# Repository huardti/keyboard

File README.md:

# zigzag keyboard

kle layout : http://www.keyboard-layout-editor.com/#/gists/5584793507362f9928e871f4f528520b

to see connections : https://kbfirmware.com/

# QMK help : 
https://github.com/qmk/keyboard_awesome

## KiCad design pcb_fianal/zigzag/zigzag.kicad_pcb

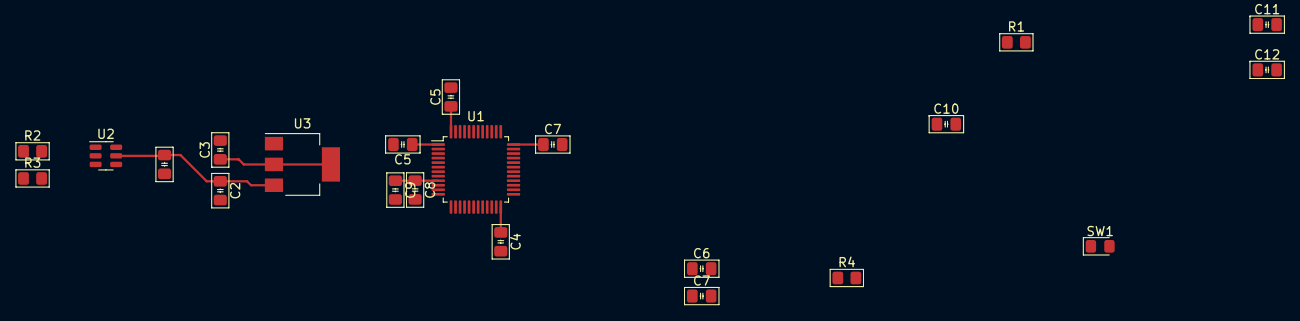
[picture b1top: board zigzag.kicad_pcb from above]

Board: 2 copper layers, 22 parts (0 on the bottom side), 5 nets.

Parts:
C1, C4, C5, C5#2, C6, C7, C7#2: 100nF; C_0805_2012Metric_Pad1.18x1.45mm_HandSolder
C2, C3: 10uF; C_0805_2012Metric_Pad1.18x1.45mm_HandSolder
C8: 1uF; C_0805_2012Metric_Pad1.18x1.45mm_HandSolder
C9: 10nF; C_0805_2012Metric_Pad1.18x1.45mm_HandSolder
C10: C_4.7uF; C_0805_2012Metric_Pad1.18x1.45mm_HandSolder
C11, C12: 30pF; C_0805_2012Metric_Pad1.18x1.45mm_HandSolder
R1: 470; R_0805_2012Metric_Pad1.20x1.40mm_HandSolder
R2, R3: 5.1k; R_0805_2012Metric_Pad1.20x1.40mm_HandSolder
R4: 10k; R_0805_2012Metric_Pad1.20x1.40mm_HandSolder
SW1: SW_Push; D_0805_2012Metric_Pad1.15x1.40mm_HandSolder
U1: STM32F303CCTx; LQFP-48_7x7mm_P0.5mm
U2: USBLC6-2SC6; SOT-23-6
U3: NCP1117-3.3_SOT223; SOT-223-3_TabPin2

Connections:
+3.3V: C3.1, C4.1, C5.1, C5#2.1, C6.1, C7.1, C7#2.1, SW1.1, U1.1 (VBAT), U1.24 (VDD), U1.36 (VDD), U1.48 (VDD), U3.2 (VO)
BOOT0: R4.2, SW1.2
GND: C1.2, C2.2, C3.2, C4.2, C5.2, C5#2.2, C6.2, C7.2, C7#2.2, C8.2, C9.2, C10.2, C11.2, C12.2, R2.1, R3.1, R4.1, U1.8 (VSSA), U1.23 (VSS), U1.35 (VSS), U1.47 (VSS), U2.2 (GND), U3.1 (GND)
unnamed: C8.1, C9.1, U1.9 (VDDA)
VBUS: C1.1, C2.1, U2.5 (VBUS), U3.3 (VI)

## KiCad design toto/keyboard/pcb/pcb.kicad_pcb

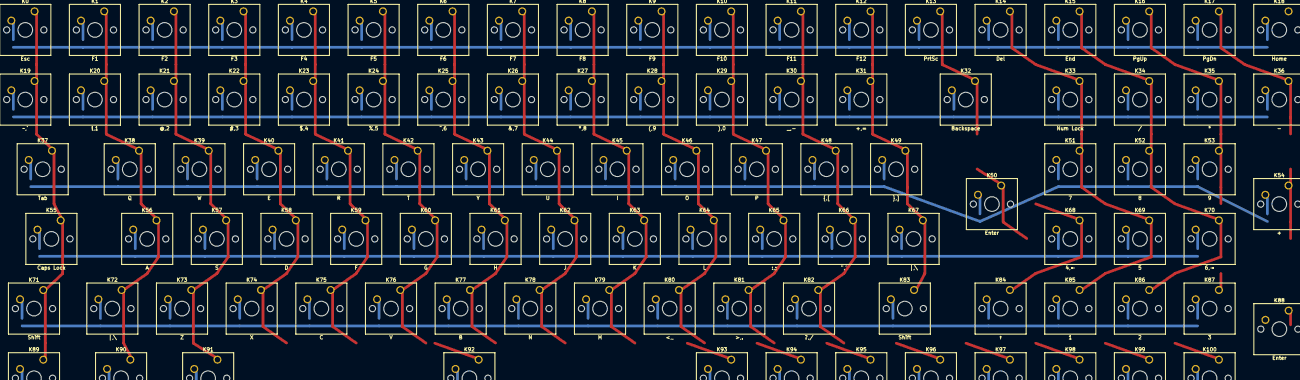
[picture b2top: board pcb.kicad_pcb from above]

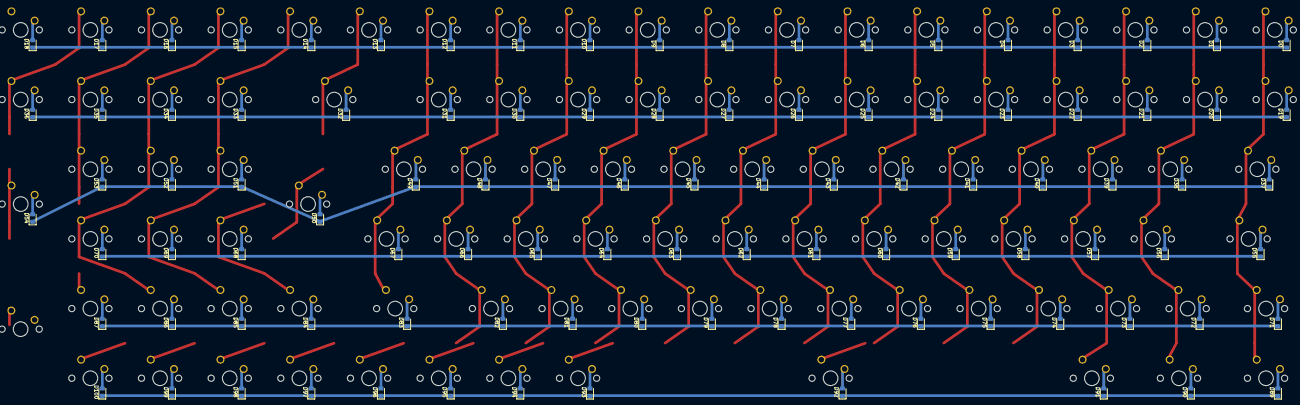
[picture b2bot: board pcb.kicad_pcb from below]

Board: 2 copper layers, 205 parts (100 on the bottom side), 124 nets.

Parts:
D0, D1, D2, D3, D4, D5, D6, D7, D8, D9, D10, D11, D12, D13, D14, D15, D16, D17, D18, D19, D20, D21, D22, D23, D24, D25, D26, D27, D28, D29, D30, D31, D32, D33, D34, D35, D36, D37, D38, D39, D40, D41, D42, D43, D44, D45, D46, D47, D48, D49, D50, D51, D52, D53, D54, D55, D56, D57, D58, D59, D60, D61, D62, D63, D64, D65, D66, D67, D68, D69, D70, D71, D72, D73, D74, D75, D76, D77, D78, D79, D80, D81, D82, D83, D84, D85, D86, D87, D89, D90, D91, D92, D93, D94, D95, D96, D97, D98, D99, D100: D; D_0805_2012Metric_Pad1.15x1.40mm_HandSolder
H1, H2, H3, H4: MountingHole; MountingHole_3.2mm_M3_DIN965
K0: Esc; SW_Cherry_MX_1.00u_PCB
K1: F1; SW_Cherry_MX_1.00u_PCB
K2: F2; SW_Cherry_MX_1.00u_PCB
K3: F3; SW_Cherry_MX_1.00u_PCB
K4: F4; SW_Cherry_MX_1.00u_PCB
K5: F5; SW_Cherry_MX_1.00u_PCB
K6: F6; SW_Cherry_MX_1.00u_PCB
K7: F7; SW_Cherry_MX_1.00u_PCB
K8: F8; SW_Cherry_MX_1.00u_PCB
K9: F9; SW_Cherry_MX_1.00u_PCB
K10: F10; SW_Cherry_MX_1.00u_PCB
K11: F11; SW_Cherry_MX_1.00u_PCB
K12: F12; SW_Cherry_MX_1.00u_PCB
K13: PrtSc; SW_Cherry_MX_1.00u_PCB
K14: Del; SW_Cherry_MX_1.00u_PCB
K15: End; SW_Cherry_MX_1.00u_PCB
K16: PgUp; SW_Cherry_MX_1.00u_PCB
K17: PgDn; SW_Cherry_MX_1.00u_PCB
K18: Home; SW_Cherry_MX_1.00u_PCB
K19: ~,`; SW_Cherry_MX_1.00u_PCB
K20: !,1; SW_Cherry_MX_1.00u_PCB
K21: @,2; SW_Cherry_MX_1.00u_PCB
K22: #,3; SW_Cherry_MX_1.00u_PCB
K23: $,4; SW_Cherry_MX_1.00u_PCB
K24: %,5; SW_Cherry_MX_1.00u_PCB
K25: ^,6; SW_Cherry_MX_1.00u_PCB
K26: &,7; SW_Cherry_MX_1.00u_PCB
K27: *,8; SW_Cherry_MX_1.00u_PCB
K28: (,9; SW_Cherry_MX_1.00u_PCB
K29: ),0; SW_Cherry_MX_1.00u_PCB
K30: _,-; SW_Cherry_MX_1.00u_PCB
K31: +,=; SW_Cherry_MX_1.00u_PCB
K32: Backspace; SW_Cherry_MX_2.00u_PCB
K33: Num Lock; SW_Cherry_MX_1.00u_PCB
K34: /; SW_Cherry_MX_1.00u_PCB
K35: *; SW_Cherry_MX_1.00u_PCB
K36: -; SW_Cherry_MX_1.00u_PCB
K37: Tab; SW_Cherry_MX_1.50u_PCB
K38: Q; SW_Cherry_MX_1.00u_PCB
K39: W; SW_Cherry_MX_1.00u_PCB
K40: E; SW_Cherry_MX_1.00u_PCB
K41: R; SW_Cherry_MX_1.00u_PCB
K42: T; SW_Cherry_MX_1.00u_PCB
K43: Y; SW_Cherry_MX_1.00u_PCB
K44: U; SW_Cherry_MX_1.00u_PCB
K45: I; SW_Cherry_MX_1.00u_PCB
K46: O; SW_Cherry_MX_1.00u_PCB
K47: P; SW_Cherry_MX_1.00u_PCB
K48: {,[; SW_Cherry_MX_1.00u_PCB
K49: },]; SW_Cherry_MX_1.00u_PCB
K50: Enter; SW_Cherry_MX_1.25u_PCB
K51: 7; SW_Cherry_MX_1.00u_PCB
K52: 8; SW_Cherry_MX_1.00u_PCB
K53: 9; SW_Cherry_MX_1.00u_PCB
K54: +; SW_Cherry_MX_1.00u_PCB
K55: Caps Lock; SW_Cherry_MX_1.75u_PCB
K56: A; SW_Cherry_MX_1.00u_PCB
K57: S; SW_Cherry_MX_1.00u_PCB
K58: D; SW_Cherry_MX_1.00u_PCB
K59: F; SW_Cherry_MX_1.00u_PCB
K60: G; SW_Cherry_MX_1.00u_PCB
K61: H; SW_Cherry_MX_1.00u_PCB
K62: J; SW_Cherry_MX_1.00u_PCB
K63: K; SW_Cherry_MX_1.00u_PCB
K64: L; SW_Cherry_MX_1.00u_PCB
K65: :,;; SW_Cherry_MX_1.00u_PCB
K66: ",'; SW_Cherry_MX_1.00u_PCB
K67, K72: |,\; SW_Cherry_MX_1.00u_PCB
K68: 4,←; SW_Cherry_MX_1.00u_PCB
K69: 5; SW_Cherry_MX_1.00u_PCB
K70: 6,→; SW_Cherry_MX_1.00u_PCB
K71: Shift; SW_Cherry_MX_1.25u_PCB
K73: Z; SW_Cherry_MX_1.00u_PCB
K74: X; SW_Cherry_MX_1.00u_PCB
K75: C; SW_Cherry_MX_1.00u_PCB
K76: V; SW_Cherry_MX_1.00u_PCB
K77: B; SW_Cherry_MX_1.00u_PCB
K78: N; SW_Cherry_MX_1.00u_PCB
K79: M; SW_Cherry_MX_1.00u_PCB
K80: <,,; SW_Cherry_MX_1.00u_PCB
K81: >,.; SW_Cherry_MX_1.00u_PCB
K82: ?,/; SW_Cherry_MX_1.00u_PCB
K83: Shift; SW_Cherry_MX_1.75u_PCB
K84: ↑; SW_Cherry_MX_1.00u_PCB
K85: 1; SW_Cherry_MX_1.00u_PCB
K86: 2; SW_Cherry_MX_1.00u_PCB
K87: 3; SW_Cherry_MX_1.00u_PCB
K88: Enter; SW_Cherry_MX_1.00u_PCB
K89: Ctrl; SW_Cherry_MX_1.25u_PCB
K90: Win; SW_Cherry_MX_1.25u_PCB
K91: Alt; SW_Cherry_MX_1.25u_PCB
K92: Blank; SW_Cherry_MX_6.25u_PCB
K93: Alt; SW_Cherry_MX_1.00u_PCB
K94: Fn; SW_Cherry_MX_1.00u_PCB
K95: Ctrl; SW_Cherry_MX_1.00u_PCB
K96: ←; SW_Cherry_MX_1.00u_PCB
K97: ↓; SW_Cherry_MX_1.00u_PCB
K98: →; SW_Cherry_MX_1.00u_PCB
K99: 0; SW_Cherry_MX_1.00u_PCB
K100: .; SW_Cherry_MX_1.00u_PCB

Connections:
/Col_0: K0.1, K19.1, K37.1, K55.1, K71.1, K89.1
/Col_1: K1.1, K20.1, K38.1, K56.1, K72.1, K90.1
/Col_2: K2.1, K21.1, K39.1, K57.1, K73.1, K91.1
/Col_3: K3.1, K22.1, K40.1, K58.1, K74.1, K92.1
/Col_4: K4.1, K23.1, K41.1, K59.1, K75.1, K93.1
/Col_5: K5.1, K24.1, K42.1, K60.1, K76.1, K94.1
/Col_6: K6.1, K25.1, K43.1, K61.1, K77.1, K95.1
/Col_7: K7.1, K26.1, K44.1, K62.1, K78.1, K96.1
/Col_8: K8.1, K27.1, K45.1, K63.1, K79.1, K97.1
/Col_9: K9.1, K28.1, K46.1, K64.1, K80.1, K98.1
/Col_10: K10.1, K29.1, K47.1, K65.1, K81.1, K99.1
/Col_11: K11.1, K30.1, K48.1, K66.1, K82.1, K100.1
/Col_12: K12.1, K31.1, K49.1, K67.1, K83.1
/Col_13: K13.1, K32.1, K50.1, K68.1, K84.1
/Col_14: K14.1, K33.1, K51.1, K69.1, K85.1
/Col_15: K15.1, K34.1, K52.1, K70.1, K86.1
/Col_16: K16.1, K35.1, K53.1, K87.1
/Col_17: K17.1, K36.1, K54.1, K88.1
/Row_0: D0.1, D1.1, D2.1, D3.1, D4.1, D5.1, D6.1, D7.1, D8.1, D9.1, D10.1 (K), D11.1 (K), D12.1 (K), D13.1 (K), D14.1 (K), D15.1 (K), D16.1 (K), D17.1 (K), D18.1 (K)
/Row_1: D19.1 (K), D20.1 (K), D21.1 (K), D22.1 (K), D23.1 (K), D24.1 (K), D25.1 (K), D26.1 (K), D27.1 (K), D28.1 (K), D29.1 (K), D30.1 (K), D31.1 (K), D32.1 (K), D33.1 (K), D34.1 (K), D35.1 (K), D36.1 (K)
/Row_2: D37.1 (K), D38.1 (K), D39.1 (K), D40.1 (K), D41.1 (K), D42.1 (K), D43.1 (K), D44.1 (K), D45.1 (K), D46.1 (K), D47.1 (K), D48.1 (K), D49.1 (K), D51.1 (K), D52.1 (K), D53.1 (K)
/Row_3: D50.1 (K), D54.1 (K), D55.1 (K), D56.1 (K), D57.1 (K), D58.1 (K), D59.1 (K), D60.1 (K), D61.1 (K), D62.1 (K), D63.1 (K), D64.1 (K), D65.1 (K), D66.1 (K), D67.1 (K), D68.1 (K), D69.1 (K), D70.1 (K)
/Row_4: D71.1 (K), D72.1 (K), D73.1 (K), D74.1 (K), D75.1 (K), D76.1 (K), D77.1 (K), D78.1 (K), D79.1 (K), D80.1 (K), D81.1 (K), D82.1 (K), D83.1 (K), D84.1 (K), D85.1 (K), D86.1 (K), D87.1 (K)
/Row_5: D89.1 (K), D90.1 (K), D91.1 (K), D92.1 (K), D93.1 (K), D94.1 (K), D95.1 (K), D96.1 (K), D97.1 (K), D98.1 (K), D99.1 (K), D100.1
unnamed: D0.2, K0.2
unnamed: D1.2, K1.2
unnamed: D2.2, K2.2
unnamed: D3.2, K3.2
unnamed: D4.2, K4.2
unnamed: D5.2, K5.2
unnamed: D6.2, K6.2
unnamed: D7.2, K7.2
unnamed: D8.2, K8.2
unnamed: D9.2, K9.2
unnamed: D10.2 (A), K10.2
unnamed: D11.2 (A), K11.2
unnamed: D12.2 (A), K12.2
unnamed: D13.2 (A), K13.2
unnamed: D14.2 (A), K14.2
unnamed: D15.2 (A), K15.2
unnamed: D16.2 (A), K16.2
unnamed: D17.2 (A), K17.2
unnamed: D18.2 (A), K18.2
unnamed: D19.2 (A), K19.2
unnamed: D20.2 (A), K20.2
unnamed: D21.2 (A), K21.2
unnamed: D22.2 (A), K22.2
unnamed: D23.2 (A), K23.2
unnamed: D24.2 (A), K24.2
unnamed: D25.2 (A), K25.2
unnamed: D26.2 (A), K26.2
unnamed: D27.2 (A), K27.2
unnamed: D28.2 (A), K28.2
unnamed: D29.2 (A), K29.2
unnamed: D30.2 (A), K30.2
unnamed: D31.2 (A), K31.2
unnamed: D32.2 (A), K32.2
unnamed: D33.2 (A), K33.2
unnamed: D34.2 (A), K34.2
unnamed: D35.2 (A), K35.2
unnamed: D36.2 (A), K36.2
unnamed: D37.2 (A), K37.2
unnamed: D38.2 (A), K38.2
unnamed: D39.2 (A), K39.2
unnamed: D40.2 (A), K40.2
unnamed: D41.2 (A), K41.2
unnamed: D42.2 (A), K42.2
unnamed: D43.2 (A), K43.2
unnamed: D44.2 (A), K44.2
unnamed: D45.2 (A), K45.2
unnamed: D46.2 (A), K46.2
unnamed: D47.2 (A), K47.2
unnamed: D48.2 (A), K48.2
unnamed: D49.2 (A), K49.2
unnamed: D50.2 (A), K50.2
unnamed: D51.2 (A), K51.2
unnamed: D52.2 (A), K52.2
unnamed: D53.2 (A), K53.2
unnamed: D54.2 (A), K54.2
unnamed: D55.2 (A), K55.2
unnamed: D56.2 (A), K56.2
unnamed: D57.2 (A), K57.2
unnamed: D58.2 (A), K58.2
unnamed: D59.2 (A), K59.2
unnamed: D60.2 (A), K60.2
unnamed: D61.2 (A), K61.2
unnamed: D62.2 (A), K62.2
unnamed: D63.2 (A), K63.2
unnamed: D64.2 (A), K64.2
unnamed: D65.2 (A), K65.2
unnamed: D66.2 (A), K66.2
unnamed: D67.2 (A), K67.2
unnamed: D68.2 (A), K68.2
unnamed: D69.2 (A), K69.2
unnamed: D70.2 (A), K70.2
unnamed: D71.2 (A), K71.2
unnamed: D72.2 (A), K72.2
unnamed: D73.2 (A), K73.2
unnamed: D74.2 (A), K74.2
unnamed: D75.2 (A), K75.2
unnamed: D76.2 (A), K76.2
unnamed: D77.2 (A), K77.2
unnamed: D78.2 (A), K78.2
unnamed: D79.2 (A), K79.2
unnamed: D80.2 (A), K80.2
unnamed: D81.2 (A), K81.2
unnamed: D82.2 (A), K82.2
unnamed: D83.2 (A), K83.2
unnamed: D84.2 (A), K84.2
unnamed: D85.2 (A), K85.2
unnamed: D86.2 (A), K86.2
unnamed: D87.2 (A), K87.2
unnamed: D89.2 (A), K89.2
unnamed: D90.2 (A), K90.2
unnamed: D91.2 (A), K91.2
unnamed: D92.2 (A), K92.2
unnamed: D93.2 (A), K93.2
unnamed: D94.2 (A), K94.2
unnamed: D95.2 (A), K95.2
unnamed: D96.2 (A), K96.2
unnamed: D97.2 (A), K97.2
unnamed: D98.2 (A), K98.2
unnamed: D99.2 (A), K99.2
unnamed: D100.2, K100.2

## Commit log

2023-04-14 lot of things
2023-04-18 update pcb
2023-12-22 toto
